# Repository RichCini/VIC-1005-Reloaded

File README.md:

# VIC-1005-Reloaded
The VIC-1005R is a 3-slot expansion backplane for the VIC-20 computer system.

The VIC-1005R (Reloaded) is a reimagination of the original but customized
for the various "reloaded" VIC-20s that have a vertical (Atari 2600-like)
expansion connector. It uses two boards -- the expansion connector board
and the multi-slot backplane -- connected by a 2x25 IDC ribbon cable.
It includes a reset switch and separate fuse to protect the backplane.

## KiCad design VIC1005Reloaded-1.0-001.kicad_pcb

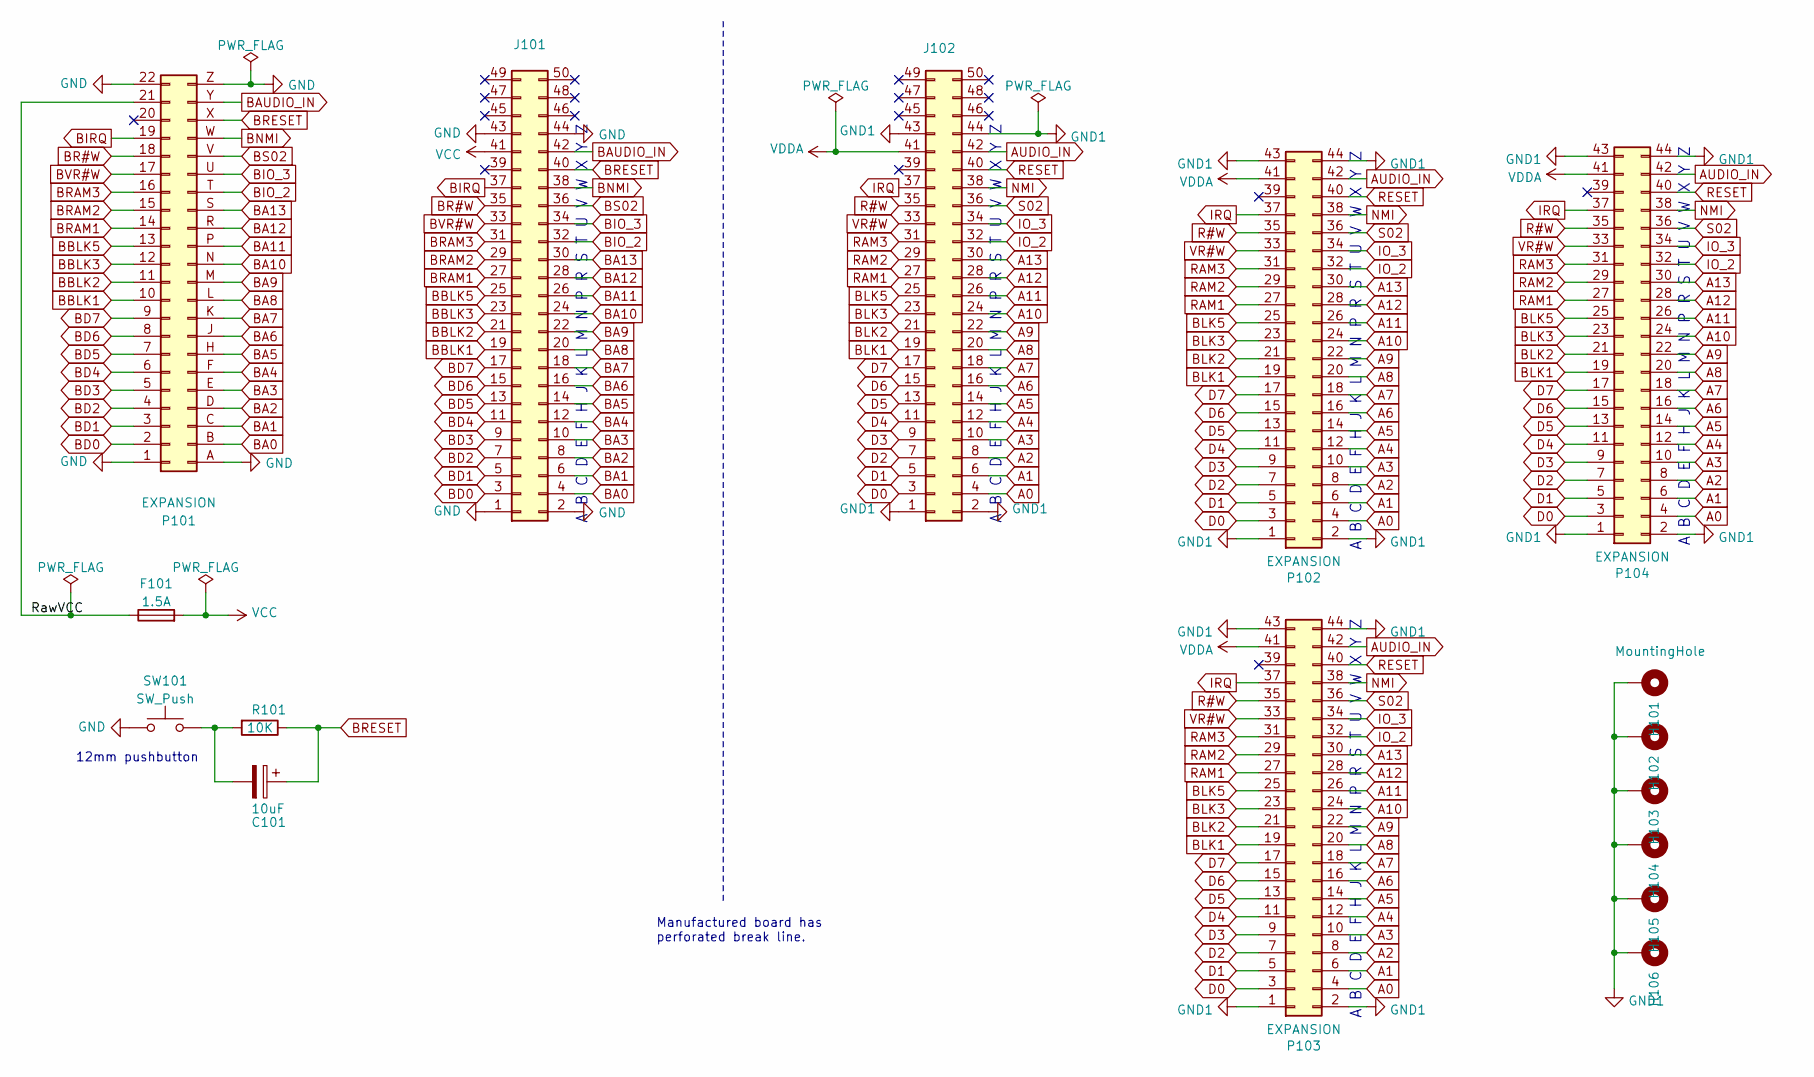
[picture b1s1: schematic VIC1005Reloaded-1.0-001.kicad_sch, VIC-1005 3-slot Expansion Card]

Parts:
C101: 10uF; CP_Radial_D4.0mm_P1.50mm
F101: 1.5A; FUSE_4527
H101, H102, H103, H104, H105, H106: MountingHole; MountingHole_3.2mm_M3_DIN965_Pad
J101, J102: (no value)
P101: EXPANSION; MA156-22-2
P102, P103, P104: EXPANSION; EDAC_02_22_Card_Edge_Connector
R101: 10K; R_Axial_DIN0207_L6.3mm_D2.5mm_P7.62mm_Horizontal
SW101: SW_Push; SW_PUSH_6mm

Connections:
/RawVCC: F101.1, P101.21
A0: J102.4, P102.4, P103.4, P104.4
A1: J102.6, P102.6, P103.6, P104.6
A2: J102.8, P102.8, P103.8, P104.8
A3: J102.10, P102.10, P103.10, P104.10
A4: J102.12, P102.12, P103.12, P104.12
A5: J102.14, P102.14, P103.14, P104.14
A6: J102.16, P102.16, P103.16, P104.16
A7: J102.18, P102.18, P103.18, P104.18
A8: J102.20, P102.20, P103.20, P104.20
A9: J102.22, P102.22, P103.22, P104.22
A10: J102.24, P102.24, P103.24, P104.24
A11: J102.26, P102.26, P103.26, P104.26
A12: J102.28, P102.28, P103.28, P104.28
A13: J102.30, P102.30, P103.30, P104.30
AUDIO_IN: J102.42, P102.42, P103.42, P104.42
BA0: J101.4, P101.B
BA1: J101.6, P101.C
BA2: J101.8, P101.D
BA3: J101.10, P101.E
BA4: J101.12, P101.F
BA5: J101.14, P101.H
BA6: J101.16, P101.J
BA7: J101.18, P101.K
BA8: J101.20, P101.L
BA9: J101.22, P101.M
BA10: J101.24, P101.N
BA11: J101.26, P101.P
BA12: J101.28, P101.R
BA13: J101.30, P101.S
BAUDIO_IN: J101.42, P101.Y
BBLK1: J101.19, P101.10
BBLK2: J101.21, P101.11
BBLK3: J101.23, P101.12
BBLK5: J101.25, P101.13
BD0: J101.3, P101.2
BD1: J101.5, P101.3
BD2: J101.7, P101.4
BD3: J101.9, P101.5
BD4: J101.11, P101.6
BD5: J101.13, P101.7
BD6: J101.15, P101.8
BD7: J101.17, P101.9
BIO_2: J101.32, P101.T
BIO_3: J101.34, P101.U
BIRQ: J101.37, P101.19
BLK1: J102.19, P102.19, P103.19, P104.19
BLK2: J102.21, P102.21, P103.21, P104.21
BLK3: J102.23, P102.23, P103.23, P104.23
BLK5: J102.25, P102.25, P103.25, P104.25
BNMI: J101.38, P101.W
BR#W: J101.35, P101.18
BRAM1: J101.27, P101.14
BRAM2: J101.29, P101.15
BRAM3: J101.31, P101.16
BRESET: C101.1, J101.40, P101.X, R101.1
BS02: J101.36, P101.V
BVR#W: J101.33, P101.17
D0: J102.3, P102.3, P103.3, P104.3
D1: J102.5, P102.5, P103.5, P104.5
D2: J102.7, P102.7, P103.7, P104.7
D3: J102.9, P102.9, P103.9, P104.9
D4: J102.11, P102.11, P103.11, P104.11
D5: J102.13, P102.13, P103.13, P104.13
D6: J102.15, P102.15, P103.15, P104.15
D7: J102.17, P102.17, P103.17, P104.17
GND: J101.1, J101.2, J101.43, J101.44, P101.1, P101.22, P101.A, P101.Z, SW101.1
GND1: H101.1, H102.1, H103.1, H104.1, H105.1, H106.1, J102.1, J102.2, J102.43, J102.44, P102.1, P102.2, P102.43, P102.44, P103.1, P103.2, P103.43, P103.44, P104.1, P104.2, P104.43, P104.44
IO_2: J102.32, P102.32, P103.32, P104.32
IO_3: J102.34, P102.34, P103.34, P104.34
IRQ: J102.37, P102.37, P103.37, P104.37
NMI: J102.38, P102.38, P103.38, P104.38
unnamed: C101.2, R101.2, SW101.2
R#W: J102.35, P102.35, P103.35, P104.35
RAM1: J102.27, P102.27, P103.27, P104.27
RAM2: J102.29, P102.29, P103.29, P104.29
RAM3: J102.31, P102.31, P103.31, P104.31
RESET: J102.40, P102.40, P103.40, P104.40
S02: J102.36, P102.36, P103.36, P104.36
VCC: F101.2, J101.41
VDDA: J102.41, P102.41, P103.41, P104.41
VR#W: J102.33, P102.33, P103.33, P104.33

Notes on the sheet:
A B C D E F H J K L M N P R S T U V W X Y Z
12mm pushbutton
Manufactured board has perforated break line.

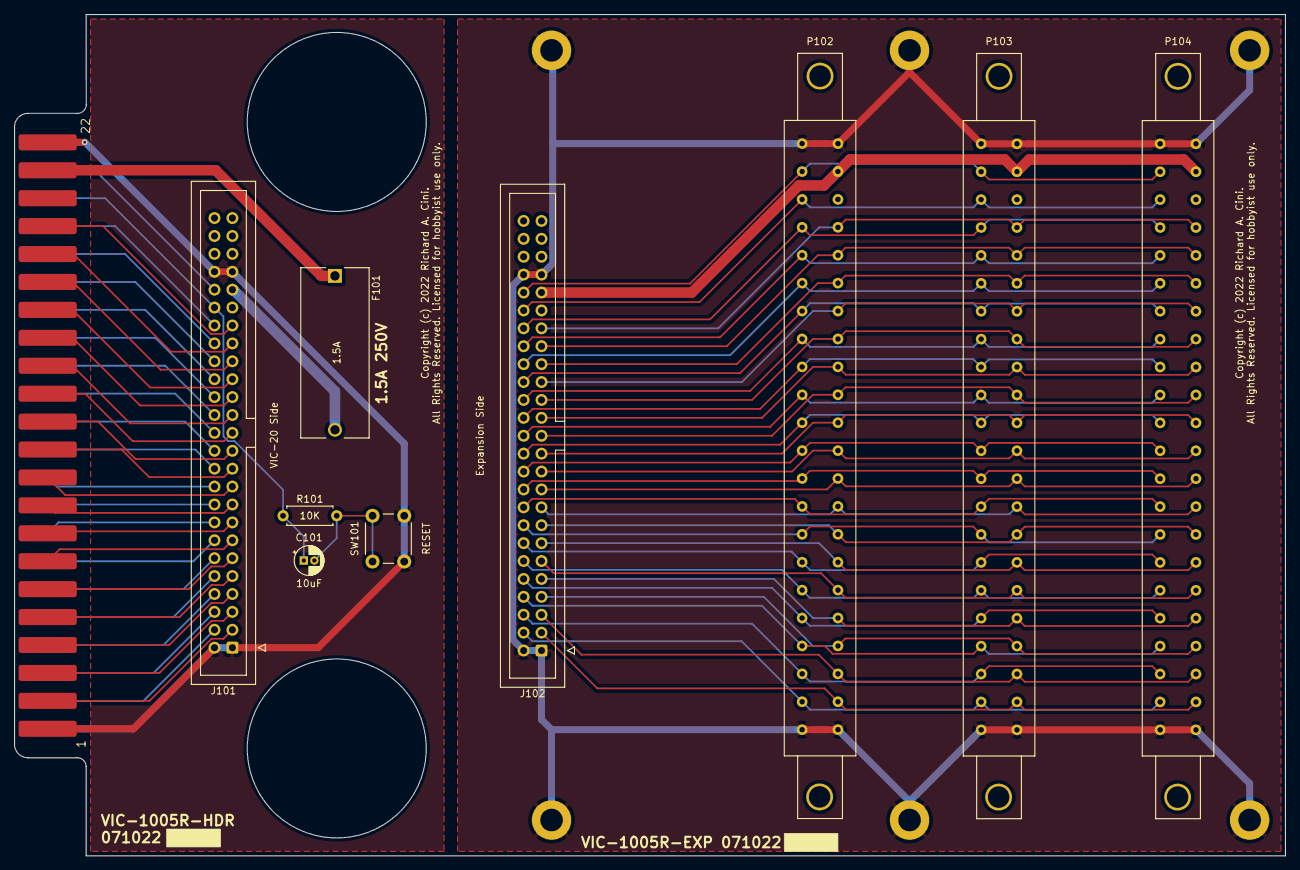
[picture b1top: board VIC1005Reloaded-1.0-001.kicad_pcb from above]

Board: 2 copper layers, 180.3 x 119.4 mm, 16 parts (0 on the bottom side), 82 nets.

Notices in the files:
VIC1005Reloaded-1.0-001.kicad_pcb:
Copyright (c) 2022 Richard A. Cini.
All Rights Reserved. Licensed for hobbyist use only.
